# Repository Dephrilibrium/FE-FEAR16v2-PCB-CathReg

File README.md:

# FEAR-Cathode Regulation
This repository contains the KiCAD-design files for a shield of the F(ield) E(mission) A(rray) R(egulation) current control circuit.

Note: This project is part of the SubModule-repository [FE-FEAR16v2][FE-FEAR16v2-SubmoduleRepo], where you can find sub-repositories for other shield-PCBs, mainboard-PCB and the firmware.

# Description
The name "cathode regulation" comes from the original main purpose of regulating the potential (extraction voltage) of a field emission array (FEA = cathode) based on the current through this cathode. However, it can be used for all purposes where a potential needs to be regulation based on the current-flow through the device under test. During active regulation this shield acts like a current-source/-sink.

- The shield itself takes 1 DAC-output voltage (V~Ctrl~ = 0..10V) to adjust the current control.
- The A(mperemeter) is actually a shunt-resistor which defines the measurable current range. A 1MΩ for instance yields a range from 0.31 nA (resolution) to 10 µA, whereby its wisely to keep the current slightly below as 10 µA is the absolute maximum measurable value.
- The V(oltmeter) measures the internal voltage-drop over the FET.

Note: Both, A and V use potentiometers to adjust their feedback-loop amplification. Due to tolerances on all the parts, its recommended to use a shield only at a specific mainboard and a specific channel-position at which the boards were calibrated.

**Principle of the cathode regulation:**

# HowTo to connect (samples and for calibration)
1. Place a shield on a mainboard/channel-slot.
2. Calibration: continue with step 3.), otherwise go to 6.)

3. Connect the positive supply of the high-voltage source to the FEA-input (see figure above) and the negative supply (GND) to the HV- input. For a fine calibration, add an amperemeter in series.

    1. Apply a high voltage to the input (e.g. 1kV) and define a V~Ctrl~ (e.g. 9V).

4. Calibrate V~Shnt~
    1. Adjust the current gain potentiometer, so that the measured ADC value divided by the shunt-resistance is equal to the amperemeter-value (V~Shnt~/R~Shunt~ = I~Amperemeter~)

5. Calibrate V~Drp~
    1. Adjust the voltage-drop gain potentiometer. The board projects a voltage range of &pm;1500V into a range of &pm;10V using a voltage divider with huge resistance values. Example for positive voltage:
    1500V * 5GΩ / 1005GΩ * Gain = 7.462..V * Gain = 10V
    Gain = 10V / 7.462..V = 1.34

6. Connect FEA on the shield's screw terminal and the most negative supply to to HV- (which is the mainboard's common-terminal).

Note: The FEAR command-documentation can be found in the firmware-repository (see [FE-FEAR16v2 Submodule-Repo][FE-FEAR16v2-SubmoduleRepo]).

[FE-FEAR16v2-SubmoduleRepo]: https://github.com/Dephrilibrium/FE-FEAR16v2

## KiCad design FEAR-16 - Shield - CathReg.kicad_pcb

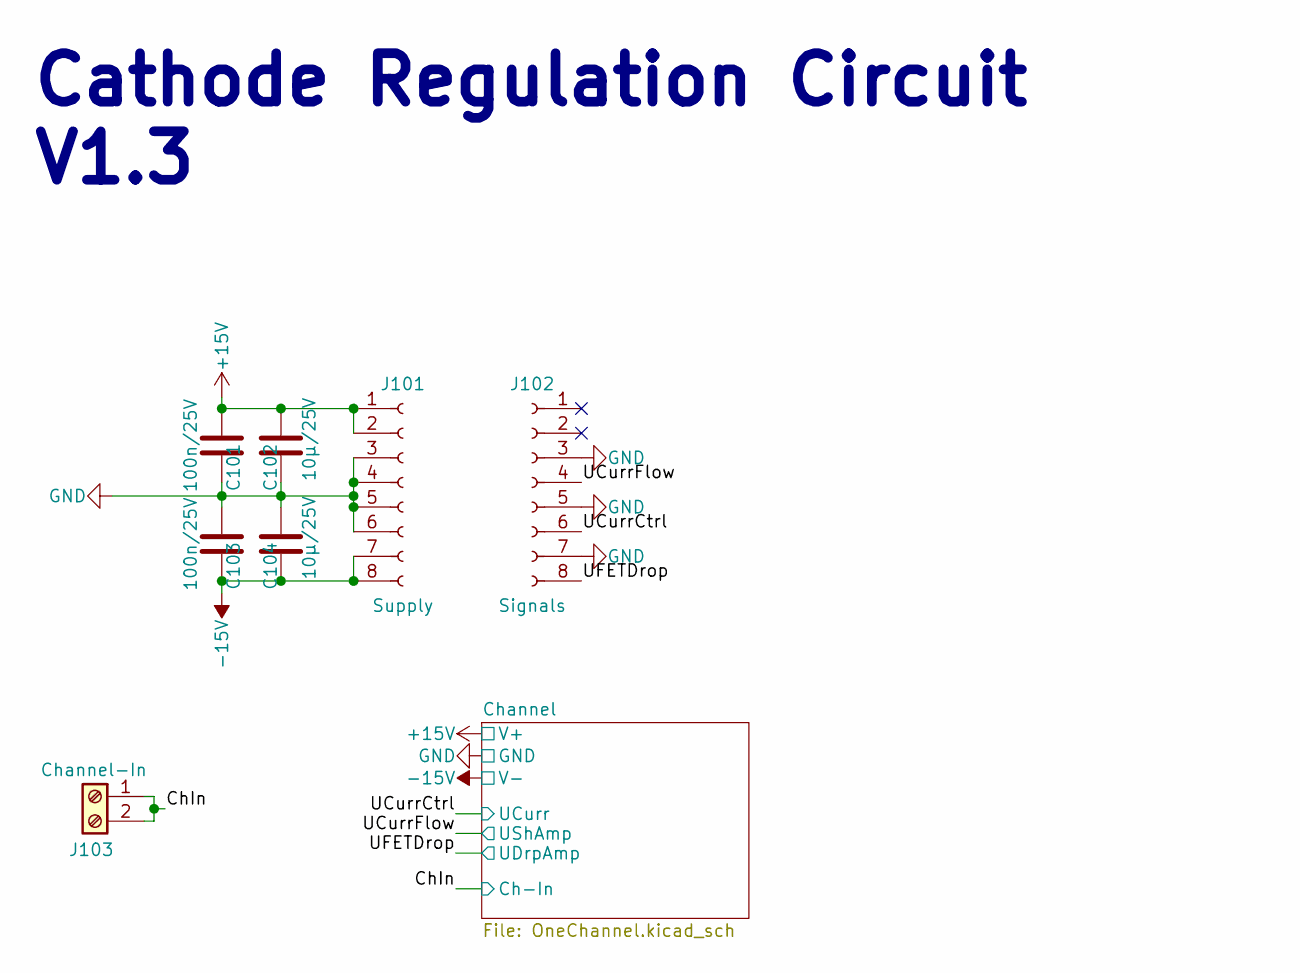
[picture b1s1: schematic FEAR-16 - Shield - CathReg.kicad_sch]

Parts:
C101, C103: 100n/25V; C_0603_1608Metric
C102, C104: 10µ/25V; C_0805_2012Metric
J101: Supply; PinHeader_1x08_P2.54mm_Vertical
J102: Signals; PinHeader_1x08_P2.54mm_Vertical
J103: Channel-In; TerminalBlock_bornier-2_P5.08mm

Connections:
+15V: C101.2, C102.2, J101.1, J101.2; also elsewhere on the board
-15V: C103.1, C104.1, J101.7, J101.8; also elsewhere on the board
/ChIn: J103.1, J103.2; also elsewhere on the board
/UCurrCtrl: J102.6; also elsewhere on the board
/UCurrFlow: J102.4; also elsewhere on the board
/UFETDrop: J102.8; also elsewhere on the board
GND: C101.1, C102.1, C103.2, C104.2, J101.3, J101.4, J101.5, J101.6, J102.3, J102.5, J102.7; also elsewhere on the board

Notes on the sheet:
Cathode Regulation Circuit V1.3

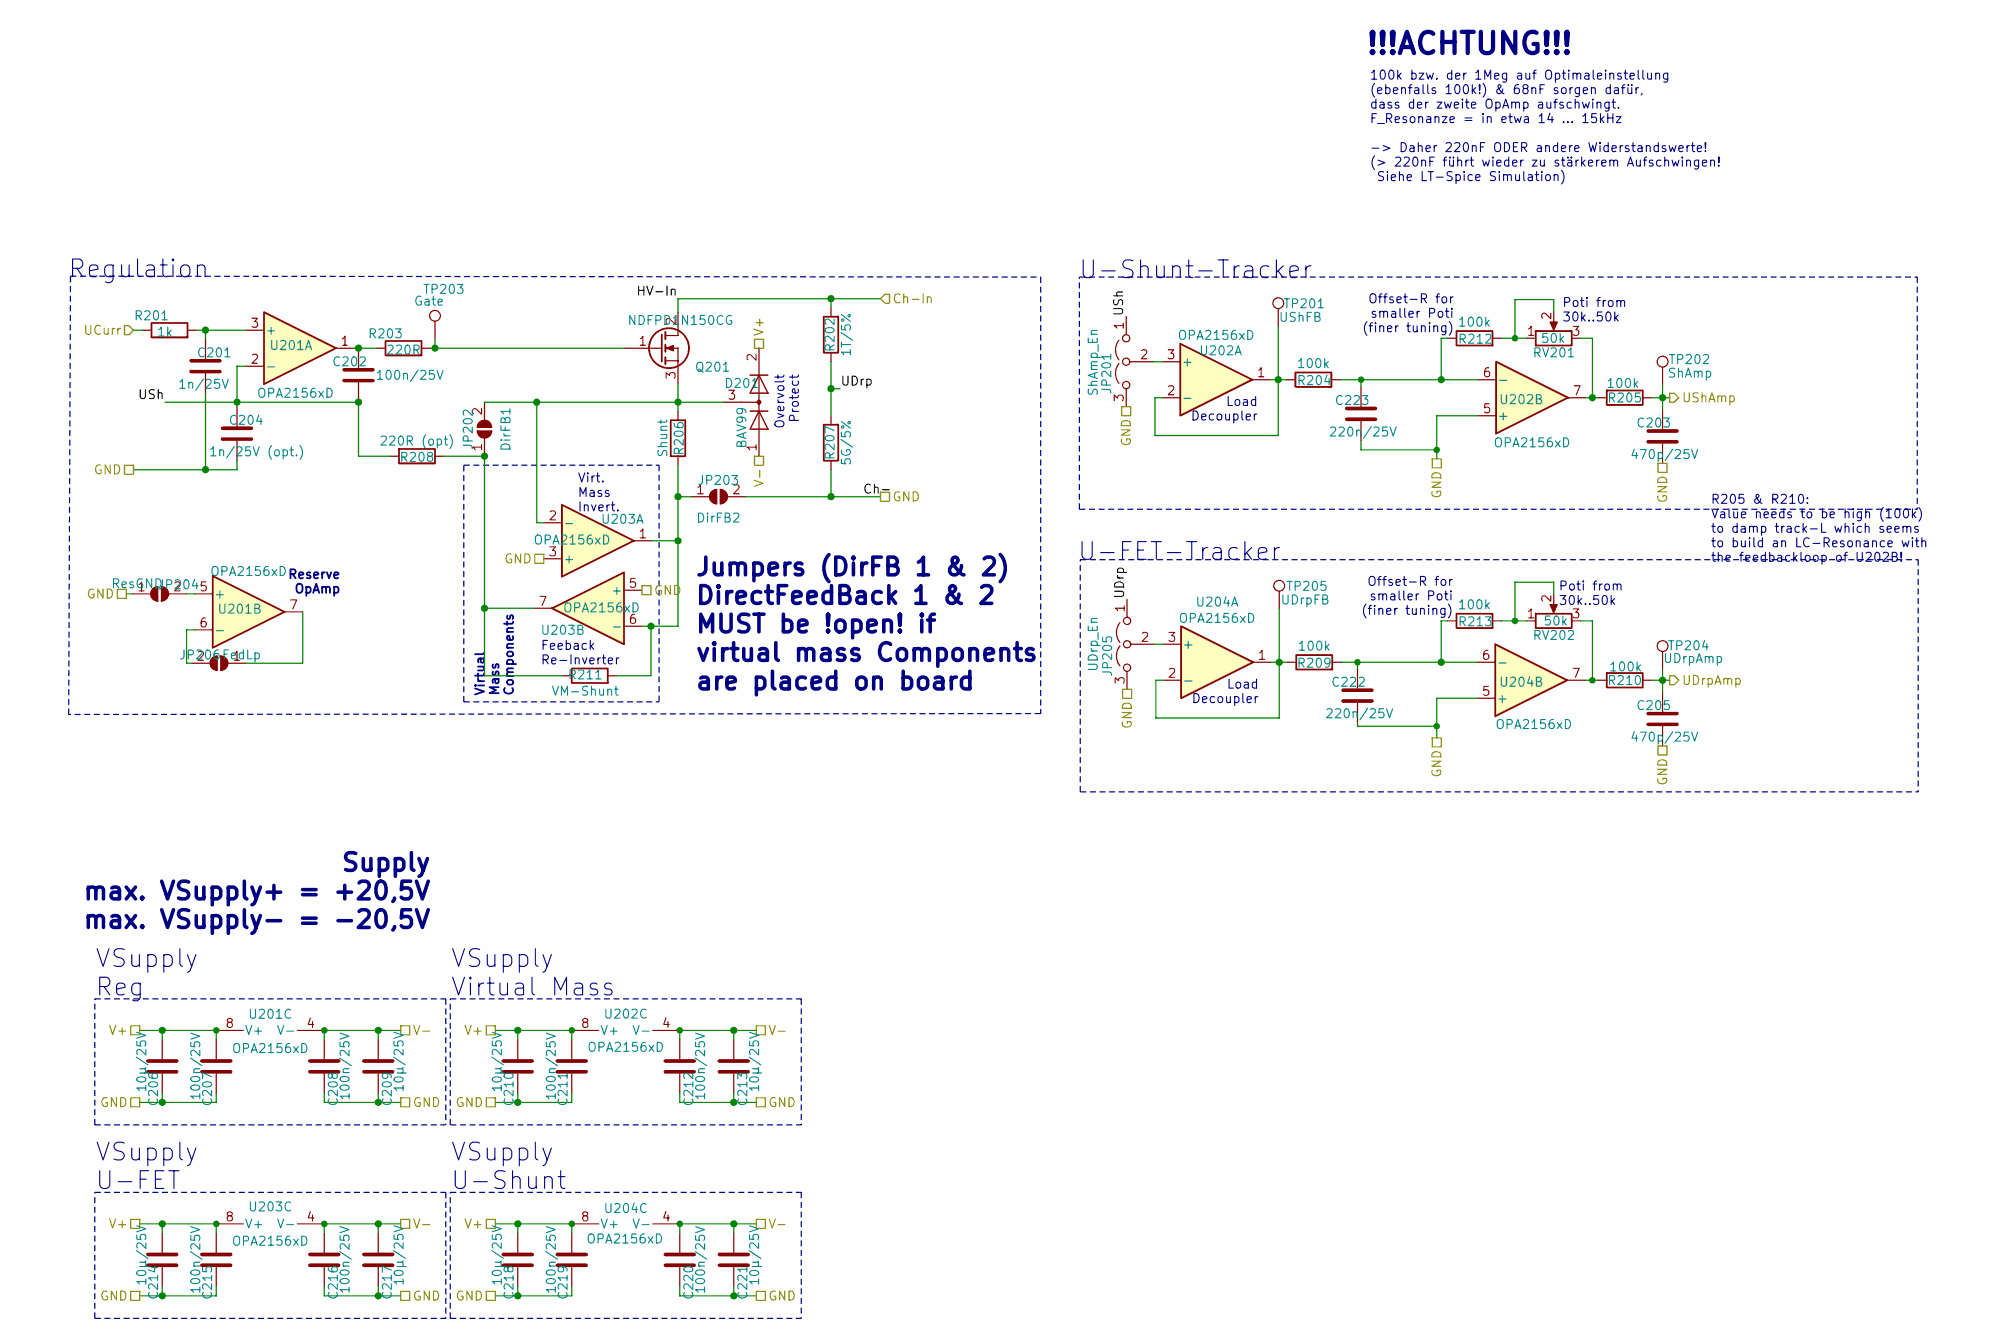
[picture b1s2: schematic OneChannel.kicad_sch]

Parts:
C201: 1n/25V; C_0603_1608Metric
C202, C207, C208, C211, C212, C215, C216, C219, C220: 100n/25V; C_0603_1608Metric
C203, C205: 470p/25V; C_0603_1608Metric
C204: 1n/25V (opt.); C_0603_1608Metric
C206, C209, C210, C213, C214, C217, C218, C221: 10µ/25V; C_0805_2012Metric
C222, C223: 220n/25V; C_0603_1608Metric
D201: BAV99; SOT-23
JP201: ShAmp_En; PinHeader_1x03_P2.54mm_Vertical
JP202: DirFB1; SolderJumper-2_P1.3mm_Open_RoundedPad1.0x1.5mm
JP203: DirFB2; SolderJumper-2_P1.3mm_Open_RoundedPad1.0x1.5mm
JP204: ResGND; SolderJumper-2_P1.3mm_Open_RoundedPad1.0x1.5mm
JP205: UDrp_En; PinHeader_1x03_P2.54mm_Vertical
JP206: FedLp; SolderJumper-2_P1.3mm_Open_RoundedPad1.0x1.5mm
Q201: NDFPD1N150CG; TO-220-3_Vertical
R201: 1k; R_0603_1608Metric
R202: 1T/5%; R_Axial_Power_L25.0mm_W6.4mm_P27.94mm
R203: 220R; R_0603_1608Metric
R204, R205, R209, R210, R212, R213: 100k; R_0603_1608Metric
R206: Shunt; R_Axial_DIN0204_L3.6mm_D1.6mm_P2.54mm_Vertical
R207: 5G/5%; R_4020_10251Metric
R208: 220R (opt); R_0603_1608Metric
R211: VM-Shunt; R_Axial_DIN0204_L3.6mm_D1.6mm_P2.54mm_Vertical
RV201, RV202: 50k; Potentiometer_Bourns_3296Y_Vertical
TP201: UShFB; TestPoint_Pad_D1.5mm
TP202: ShAmp; TestPoint_Pad_D1.5mm
TP203: Gate; TestPoint_Pad_D1.5mm
TP204: UDrpAmp; TestPoint_Pad_D1.5mm
TP205: UDrpFB; TestPoint_Pad_D1.5mm
U201, U202, U203, U204: OPA2156xD; SOIC-8_3.9x4.9mm_P1.27mm

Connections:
+15V: C206.2, C207.2, C210.2, C211.2, C214.2, C215.2, C218.2, C219.2, D201.2 (A), U201.8 (V+), U202.8 (V+), U203.8 (V+), U204.8 (V+); also elsewhere on the board
-15V: C208.2, C209.2, C212.2, C213.2, C216.2, C217.2, C220.2, C221.2, D201.1 (K), U201.4 (V-), U202.4 (V-), U203.4 (V-), U204.4 (V-); also elsewhere on the board
/ChIn: Q201.2 (D), R202.2; also elsewhere on the board
/Channel/UDrp: JP205.1 (A), R202.1, R207.2
/Channel/USh: C202.1, C204.2, JP201.1 (A), R208.2, U201.2 (-)
/UCurrCtrl: R201.1; also elsewhere on the board
/UCurrFlow: C203.2, R205.1, TP202.1; also elsewhere on the board
/UFETDrop: C205.2, R210.1, TP204.1; also elsewhere on the board
GND: C201.2, C203.1, C204.1, C205.1, C206.1, C207.1, C208.1, C209.1, C210.1, C211.1, C212.1, C213.1, C214.1, C215.1, C216.1, C217.1, C218.1, C219.1, C220.1, C221.1, C222.1, C223.1, JP201.3 (B), JP203.2 (B), JP204.1 (A), JP205.3 (B), R207.1, U202.5 (+), U203.3 (+), U203.5 (+), U204.5 (+); also elsewhere on the board
unnamed: C202.2, R203.1, U201.1
unnamed: JP201.2 (C), U202.3 (+)
unnamed: JP202.1 (A), R208.1, R211.1, U203.7
unnamed: D201.3 (K), JP202.2 (B), Q201.3 (S), R206.1, U203.2 (-)
unnamed: JP203.1 (A), R206.2, R211.2, U203.1, U203.6 (-)
unnamed: JP204.2 (B), U201.5 (+)
unnamed: JP205.2 (C), U204.3 (+)
unnamed: JP206.1 (A), U201.7
unnamed: JP206.2 (B), U201.6 (-)
unnamed: Q201.1 (G), R203.2, TP203.1
unnamed: R205.2, RV201.3, U202.7
unnamed: R210.2, RV202.3, U204.7
unnamed: R212.2, RV201.1, RV201.2
unnamed: R213.2, RV202.1, RV202.2
unnamed: C201.1, R201.2, U201.3 (+)
unnamed: R204.1, TP201.1, U202.1, U202.2 (-)
unnamed: C223.2, R204.2, R212.1, U202.6 (-)
unnamed: R209.1, TP205.1, U204.1, U204.2 (-)
unnamed: C222.2, R209.2, R213.1, U204.6 (-)

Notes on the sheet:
Feeback Re-Inverter
Load Decoupler
Virtual Mass Components
Poti from 30k..50k
VSupply U-Shunt
VSupply Virtual Mass
U-Shunt-Tracker
VSupply U-FET
Overvolt Protect
Offset-R for smaller Poti (finer tuning)
VSupply Reg
Supply max. VSupply+ = +20,5V max. VSupply- = -20,5V
R205 & R210: Value needs to be high (100k) to damp track-L which seems to build an LC-Resonance with the feedbackloop of U202B!
Reserve OpAmp
U-FET-Tracker
100k bzw. der 1Meg auf Optimaleinstellung (ebenfalls 100k!) & 68nF sorgen dafür, dass der zweite OpAmp aufschwingt. F_Resonanze = in etwa 14 ... 15kHz -> Daher 220nF ODER andere Widerstandswerte! (> 220nF führt wieder zu stärkerem Aufschwingen! Siehe LT-Spice Simulation)
Regulation
!!!ACHTUNG!!!
Jumpers (DirFB 1 & 2) DirectFeedBack 1 & 2 MUST be !open! if virtual mass Components are placed on board
Virt. Mass Invert.

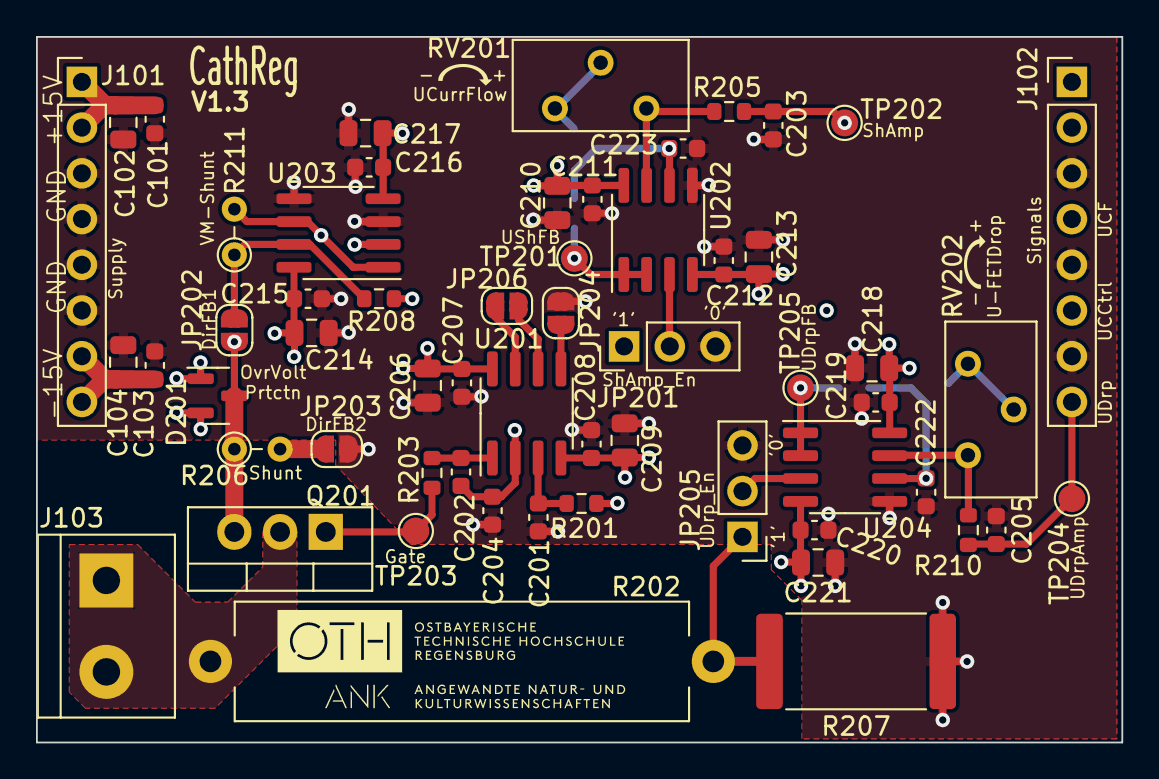
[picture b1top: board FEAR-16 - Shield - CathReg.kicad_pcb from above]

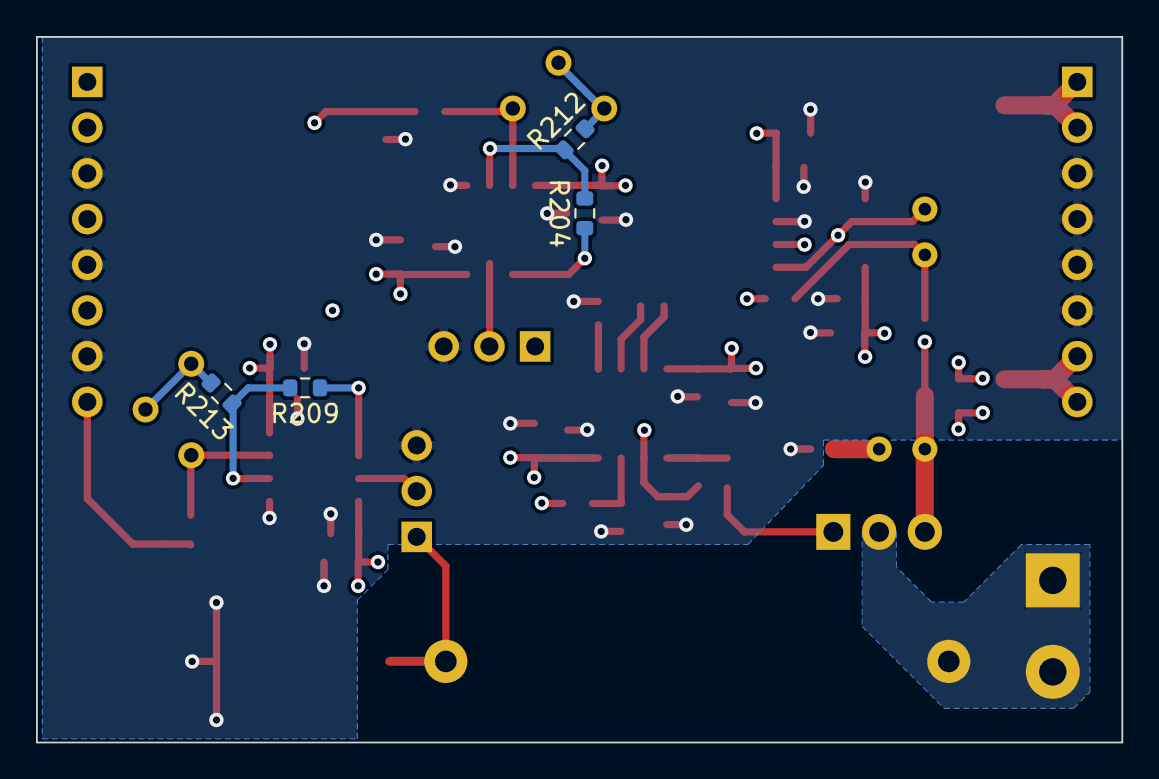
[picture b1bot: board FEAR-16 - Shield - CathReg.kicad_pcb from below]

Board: 4 copper layers, 60.3 x 39.2 mm, 62 parts (4 on the bottom side), 28 nets.

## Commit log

2023-07-20 V1.3 (improved fine-tuning of CF- and UD-Amps)
    PCB Changes:
    - Amplification Poti (1Meg) changed to Offset-Resistor (100k) + Poti (50k) to achieve 20x finer tuning of the amplification
    Misc.:
    - Fixed .gitignore to ignore the prl files
2023-07-20 Added LICENSE.md
2023-07-26 Added offset resistor in row to poti for finer tuning of the measurement amplification
2023-09-01 Specified resistor and poti with the values of the buyed ones
2024-06-11 Removed C202 and adjusted .gitignore
    - Added new temporary files to .gitignore
    - C202 is not applicable for this circuit and was removed (now an optional part)
    - Now using KiCAD 8 (new Project, Board, Schematic files mostly change a bit)
2024-09-12 Added comments on the UDrp feedback-loop
2024-09-13 Modified .gitignore and finished initial README.md
